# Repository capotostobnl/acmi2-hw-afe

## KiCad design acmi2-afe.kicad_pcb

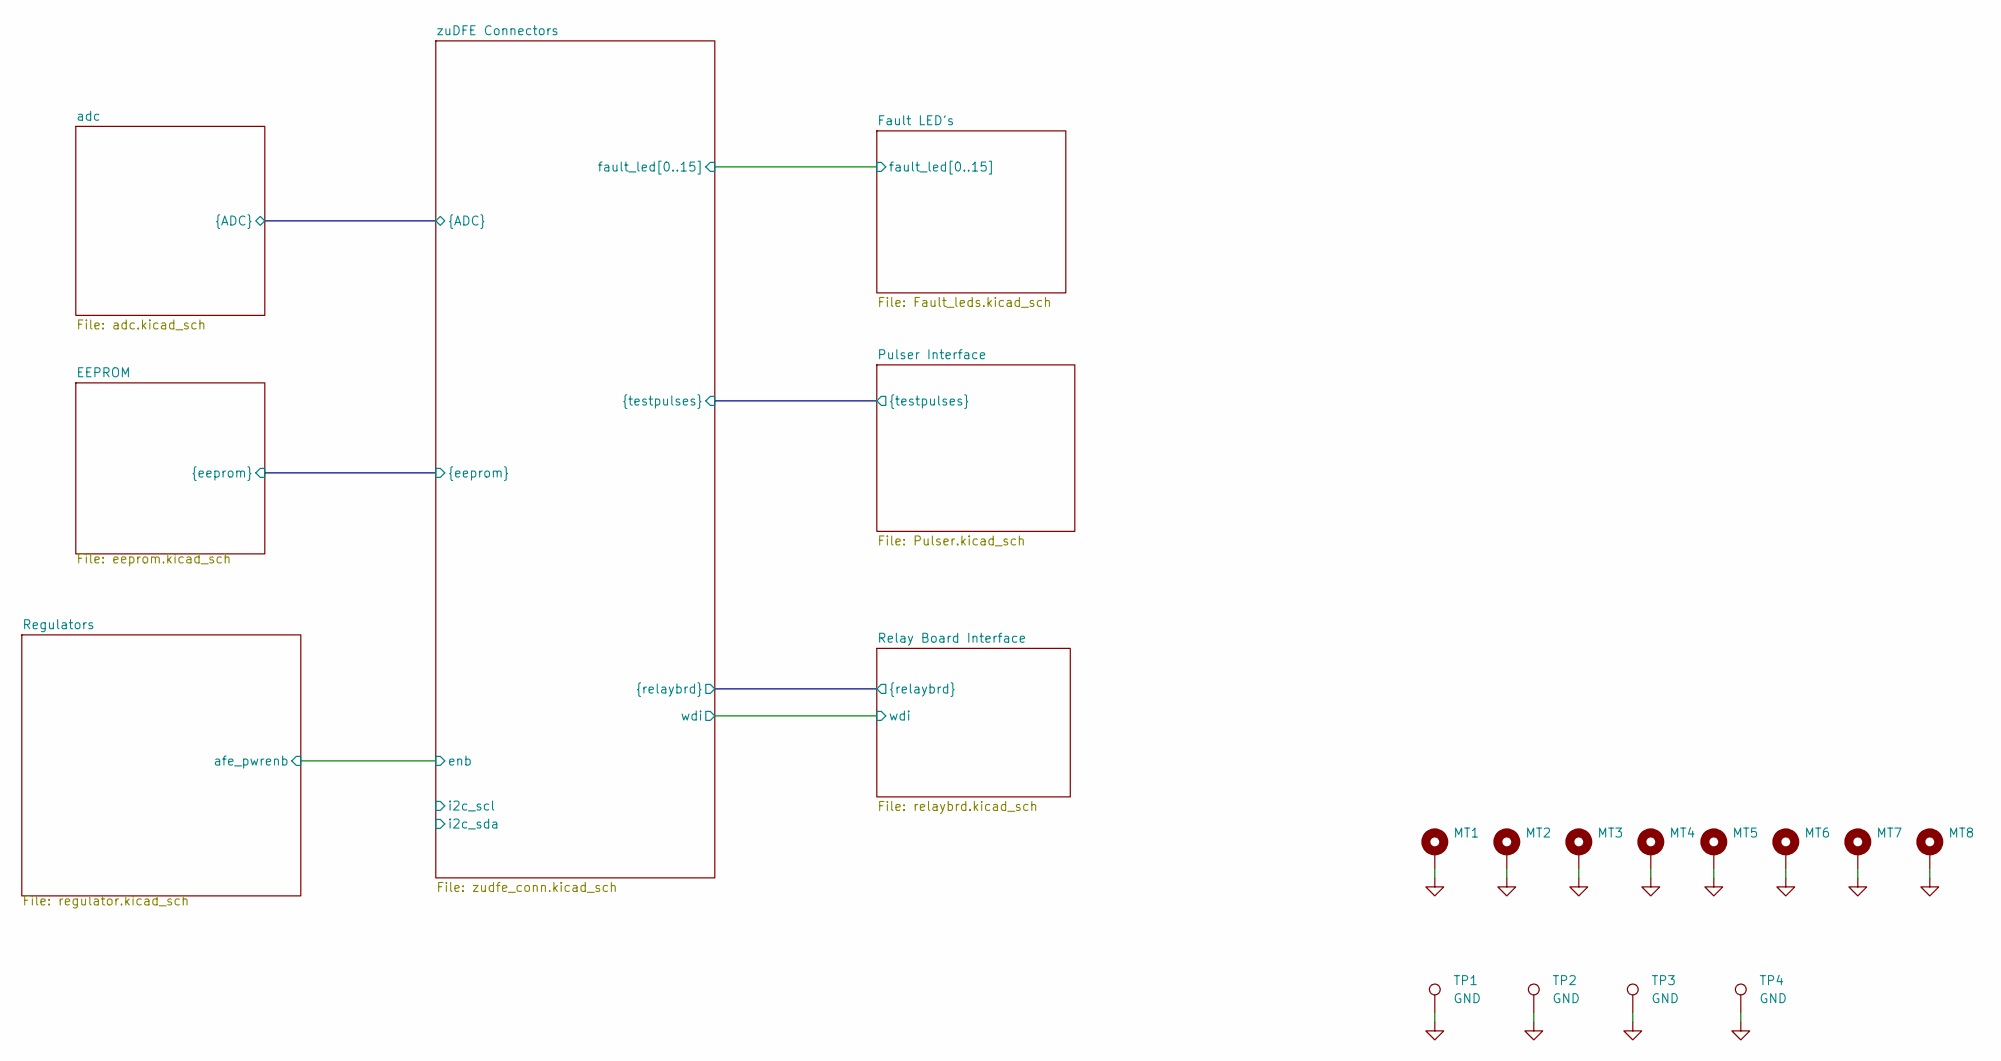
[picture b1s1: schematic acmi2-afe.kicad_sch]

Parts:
MT1, MT2, MT3, MT4, MT5, MT6, MT7, MT8: MountingHole_Pad; MountingHole_4.3mm_M4_DIN965_Pad
TP1, TP2, TP3, TP4: GND; TestPoint_RCS-0C; MFG_PN RCS-0C

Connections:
GND: MT1.1, MT2.1, MT3.1, MT4.1, MT5.1, MT6.1, MT7.1, MT8.1, TP1.1, TP2.1, TP3.1, TP4.1; also elsewhere on the board

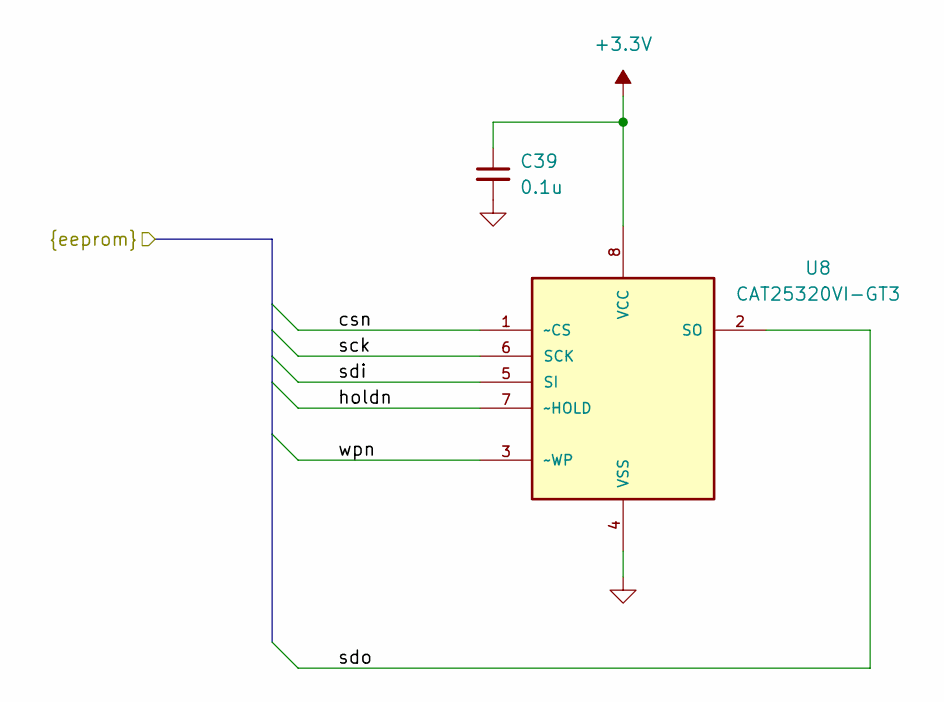
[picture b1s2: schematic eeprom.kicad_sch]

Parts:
C39: 0.1u; C_0805_2012Metric; MFG_PN TMF212B7104KGHT
U8: CAT25320VI-GT3; SOIC127P600X175-8N; MFG_PN CAT25320VI-GT3

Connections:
+3.3V: C39.1, U8.8 (VCC); also elsewhere on the board
/EEPROM/csn: U8.1 (~CS); also elsewhere on the board
/EEPROM/holdn: U8.7 (~HOLD); also elsewhere on the board
/EEPROM/sck: U8.6 (SCK); also elsewhere on the board
/EEPROM/sdi: U8.5 (SI); also elsewhere on the board
/EEPROM/sdo: U8.2 (SO); also elsewhere on the board
/EEPROM/wpn: U8.3 (~WP); also elsewhere on the board
GND: C39.2, U8.4 (VSS); also elsewhere on the board

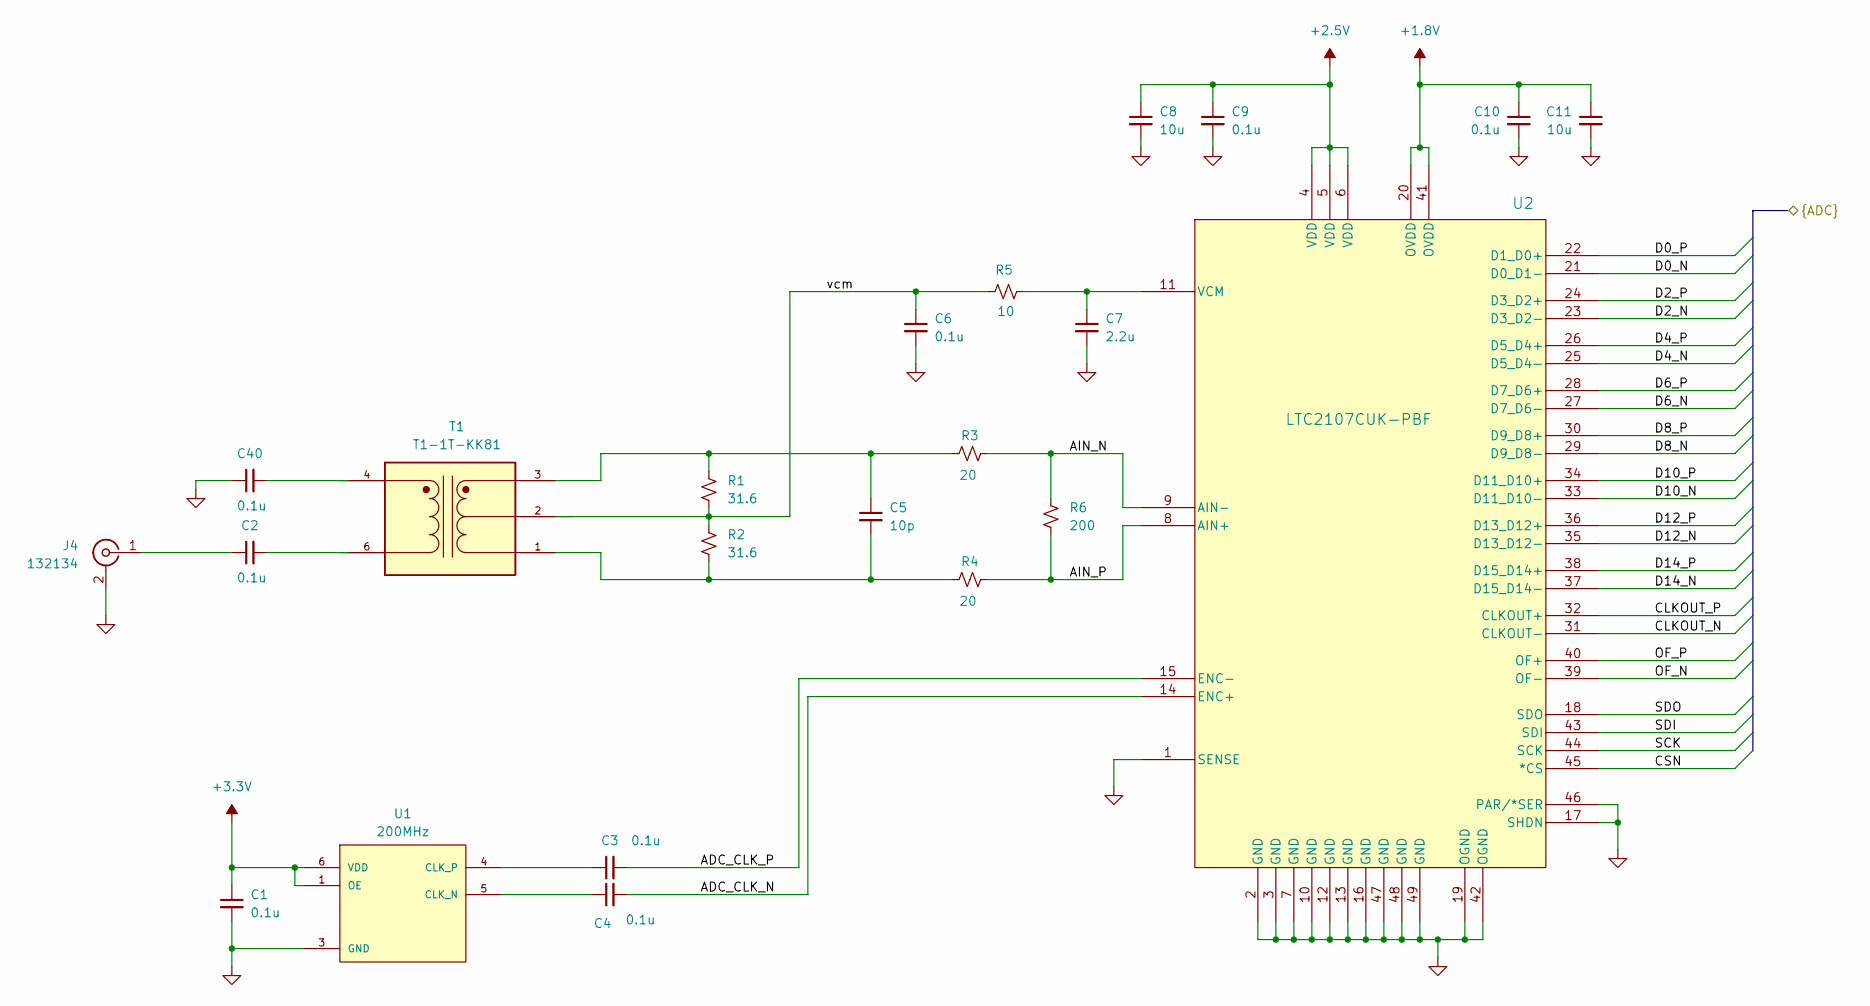
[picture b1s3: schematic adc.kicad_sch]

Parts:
C1, C2, C3, C4, C6, C9, C10, C40: 0.1u; C_0805_2012Metric; MFG_PN TMF212B7104KGHT
C5: 10p; C_0805_2012Metric; MFG_PN QVS212CG100JDHT
C7: 2.2u; C_0805_2012Metric; MFG_PN UMK212BB7225KG-T
C8, C11: 10u; C_0805_2012Metric; MFG_PN GRM21BR61C106KE15K
J4: 132134; SMA_Amphenol_132134_Vertical; MFG_PN 132134
R1, R2: 31.6; R_0805_2012Metric; MFG_PN ERJ-6ENF31R6V
R3, R4: 20; R_0805_2012Metric; MFG_PN ERJ-6ENF20R0V
R5: 10; R_0805_2012Metric; MFG_PN ERJ-6ENF10R0V
R6: 200; R_0805_2012Metric; MFG_PN ERJ-6ENF2000V
T1: T1-1T-KK81; XFMR_T1-1T-KK81_; PARTREV B
U1: 200MHz; OSC_ECS-LVDS33-2000-BN; MFG_PN ECS-LVDS33-2000-BN
U2: LTC2107CUK-PBF; QFN-48_UK_LIT; MFG_PN LTC2107CUK#PBF

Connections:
+1.8V: C10.1, C11.1, U2.20 (OVDD), U2.41 (OVDD); also elsewhere on the board
+2.5V: C8.1, C9.1, U2.4 (VDD), U2.5 (VDD), U2.6 (VDD); also elsewhere on the board
+3.3V: C1.1, U1.1 (OE), U1.6 (VDD); also elsewhere on the board
/adc/ADC_CLK_N: C4.2, U2.14 (ENC+)
/adc/ADC_CLK_P: C3.2, U2.15 (ENC-)
/adc/AIN_N: R3.1, R6.1, U2.9 (AIN-)
/adc/AIN_P: R4.1, R6.2, U2.8 (AIN+)
/adc/CLKOUT_N: U2.31 (CLKOUT-); also elsewhere on the board
/adc/CLKOUT_P: U2.32 (CLKOUT+); also elsewhere on the board
/adc/CSN: U2.45 (*CS); also elsewhere on the board
/adc/D0_N: U2.21 (D0_D1-); also elsewhere on the board
/adc/D0_P: U2.22 (D1_D0+); also elsewhere on the board
/adc/D2_N: U2.23 (D3_D2-); also elsewhere on the board
/adc/D2_P: U2.24 (D3_D2+); also elsewhere on the board
/adc/D4_N: U2.25 (D5_D4-); also elsewhere on the board
/adc/D4_P: U2.26 (D5_D4+); also elsewhere on the board
/adc/D6_N: U2.27 (D7_D6-); also elsewhere on the board
/adc/D6_P: U2.28 (D7_D6+); also elsewhere on the board
/adc/D8_N: U2.29 (D9_D8-); also elsewhere on the board
/adc/D8_P: U2.30 (D9_D8+); also elsewhere on the board
/adc/D10_N: U2.33 (D11_D10-); also elsewhere on the board
/adc/D10_P: U2.34 (D11_D10+); also elsewhere on the board
/adc/D12_N: U2.35 (D13_D12-); also elsewhere on the board
/adc/D12_P: U2.36 (D13_D12+); also elsewhere on the board
/adc/D14_N: U2.37 (D15_D14-); also elsewhere on the board
/adc/D14_P: U2.38 (D15_D14+); also elsewhere on the board
/adc/OF_N: U2.39 (OF-); also elsewhere on the board
/adc/OF_P: U2.40 (OF+); also elsewhere on the board
/adc/SCK: U2.44 (SCK); also elsewhere on the board
/adc/SDI: U2.43 (SDI); also elsewhere on the board
/adc/SDO: U2.18 (SDO); also elsewhere on the board
/adc/vcm: C6.1, R1.2, R2.1, R5.2, T1.2
GND: C1.2, C6.2, C7.2, C8.2, C9.2, C10.2, C11.2, C40.1, J4.2 (Ext), U1.3 (GND), U2.1 (SENSE), U2.2 (GND), U2.3 (GND), U2.7 (GND), U2.10 (GND), U2.12 (GND), U2.13 (GND), U2.16 (GND), U2.17 (SHDN), U2.19 (OGND), U2.42 (OGND), U2.46 (PAR/*SER), U2.47 (GND), U2.48 (GND), U2.49 (GND); also elsewhere on the board
unnamed: C2.2, T1.6
unnamed: C5.1, R1.1, R3.2, T1.3
unnamed: C5.2, R2.2, R4.2, T1.1
unnamed: C40.2, T1.4
unnamed: C2.1, J4.1 (In)
unnamed: C4.1, U1.5 (CLK_N)
unnamed: C3.1, U1.4 (CLK_P)
unnamed: C7.1, R5.1, U2.11 (VCM)

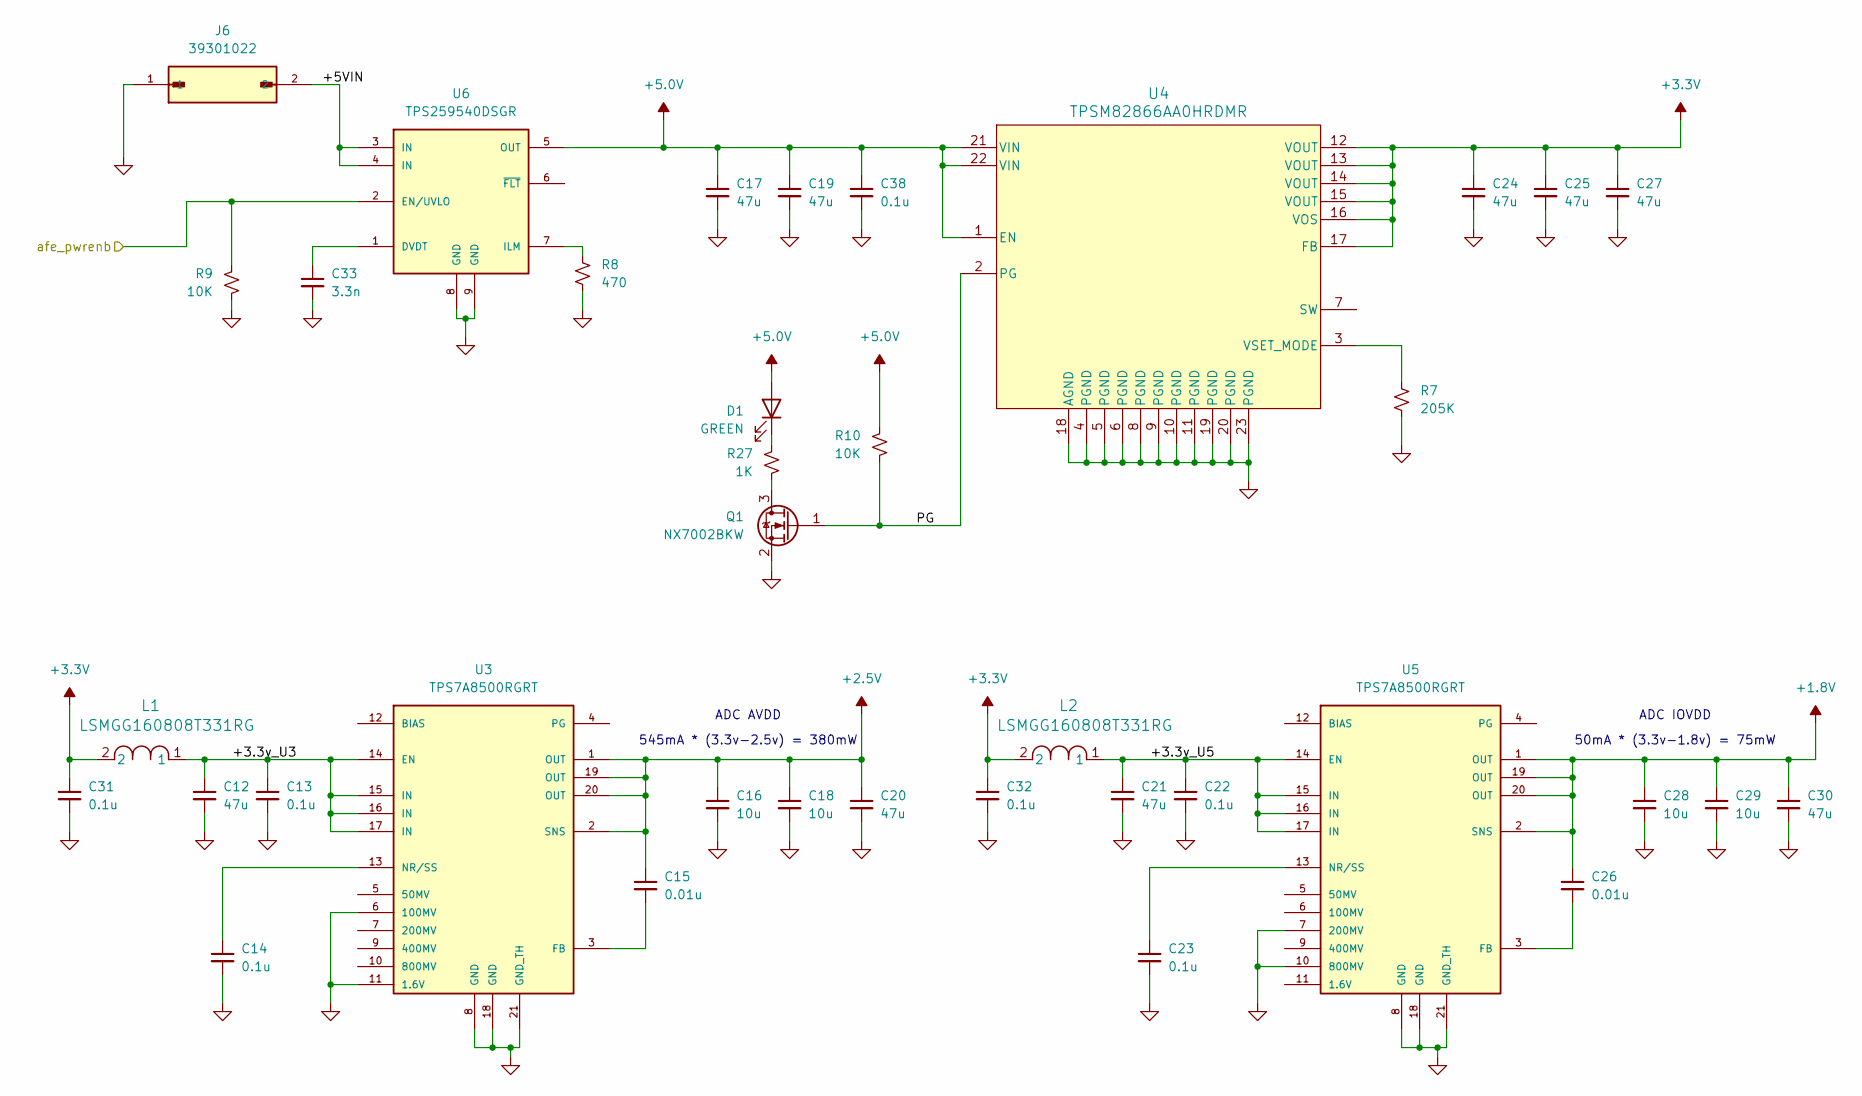
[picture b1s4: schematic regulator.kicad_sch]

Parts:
C12, C17, C19, C20, C21, C24, C25, C27, C30: 47u; C_0805_2012Metric; MFG_PN C2012X5R1A476M125AC
C13, C14, C22, C23, C31, C32, C38: 0.1u; C_0805_2012Metric; MFG_PN TMF212B7104KGHT
C15, C26: 0.01u; C_0805_2012Metric; MFG_PN MAASU21GSL8103MTNA01
C16, C18, C28, C29: 10u; C_0805_2012Metric; MFG_PN GRM21BR61C106KE15K
C33: 3.3n; C_0805_2012Metric; MFG_PN C0805X332K5RECTU
D1: GREEN; LED_0805_2012Metric; MFG_PN LTST-C191KGKT
J6: 39301022; MOLEX_39301022; PARTREV A
L1, L2: LSMGG160808T331RG; IND_LSMG_160808_TAY; MFG_PN LSMGG160808T331RG
Q1: NX7002BKW; SOT-323_SC-70; MFG_PN NX7002BKWX
R7: 205K; R_0805_2012Metric; MFG_PN ERJ-6ENF2053V
R8: 470; R_0805_2012Metric; MFG_PN ERJ-6ENF4700V
R9, R10: 10K; R_0805_2012Metric; MFG_PN ERJ-2RKF1001X
R27: 1K; R_0805_2012Metric; MFG_PN ERJ-P06F1001V
U3, U5: TPS7A8500RGRT; QFN50P350X350X100-21N; MFG_PN TPS7A8500RGRT
U4: TPSM82866AA0HRDMR; RDM0023A-MFG; MFG_PN TPSM82866AA0HRDMR
U6: TPS259540DSGR; SON50P200X200X80-9N; MFG_PN TPS259540DSGR

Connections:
+1.8V: C26.1, C28.1, C29.1, C30.1, U5.1 (OUT), U5.2 (SNS), U5.19 (OUT), U5.20 (OUT); also elsewhere on the board
+2.5V: C15.1, C16.1, C18.1, C20.1, U3.1 (OUT), U3.2 (SNS), U3.19 (OUT), U3.20 (OUT); also elsewhere on the board
+3.3V: C24.1, C25.1, C27.1, C31.1, C32.1, L1.2, L2.2, U4.12 (VOUT), U4.13 (VOUT), U4.14 (VOUT), U4.15 (VOUT), U4.16 (VOS), U4.17 (FB); also elsewhere on the board
+5.0V: C17.1, C19.1, C38.1, D1.2 (A), R10.1, U4.1 (EN), U4.21 (VIN), U4.22 (VIN), U6.5 (OUT); also elsewhere on the board
/Regulators/+3.3v_U3: C12.1, C13.1, L1.1, U3.14 (EN), U3.15 (IN), U3.16 (IN), U3.17 (IN)
/Regulators/+3.3v_U5: C21.1, C22.1, L2.1, U5.14 (EN), U5.15 (IN), U5.16 (IN), U5.17 (IN)
/Regulators/+5VIN: J6.2, U6.3 (IN), U6.4 (IN)
/Regulators/PG: Q1.1 (G), R10.2, U4.2 (PG)
/Regulators/afe_pwrenb: R9.1, U6.2 (EN/UVLO); also elsewhere on the board
GND: C12.2, C13.2, C14.2, C16.2, C17.2, C18.2, C19.2, C20.2, C21.2, C22.2, C23.2, C24.2, C25.2, C27.2, C28.2, C29.2, C30.2, C31.2, C32.2, C33.2, C38.2, J6.1, Q1.2 (S), R7.2, R8.2, R9.2, U3.6 (100MV), U3.8 (GND), U3.11 (1.6V), U3.18 (GND), U3.21 (GND_TH), U4.4 (PGND), U4.5 (PGND), U4.6 (PGND), U4.8 (PGND), U4.9 (PGND), U4.10 (PGND), U4.11 (PGND), U4.18 (AGND), U4.19 (PGND), U4.20 (PGND), U4.23 (PGND), U5.7 (200MV), U5.8 (GND), U5.10 (800MV), U5.18 (GND), U5.21 (GND_TH), U6.8 (GND), U6.9 (GND); also elsewhere on the board
unnamed: D1.1 (K), R27.1
unnamed: Q1.3 (D), R27.2
unnamed: C15.2, U3.3 (FB)
unnamed: C14.1, U3.13 (NR/SS)
unnamed: R7.1, U4.3 (VSET_MODE)
unnamed: C26.2, U5.3 (FB)
unnamed: C23.1, U5.13 (NR/SS)
unnamed: C33.1, U6.1 (DVDT)
unnamed: R8.1, U6.7 (ILM)

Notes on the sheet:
50mA * (3.3v-1.8v) = 75mW
ADC IOVDD
ADC AVDD
545mA * (3.3v-2.5v) = 380mW

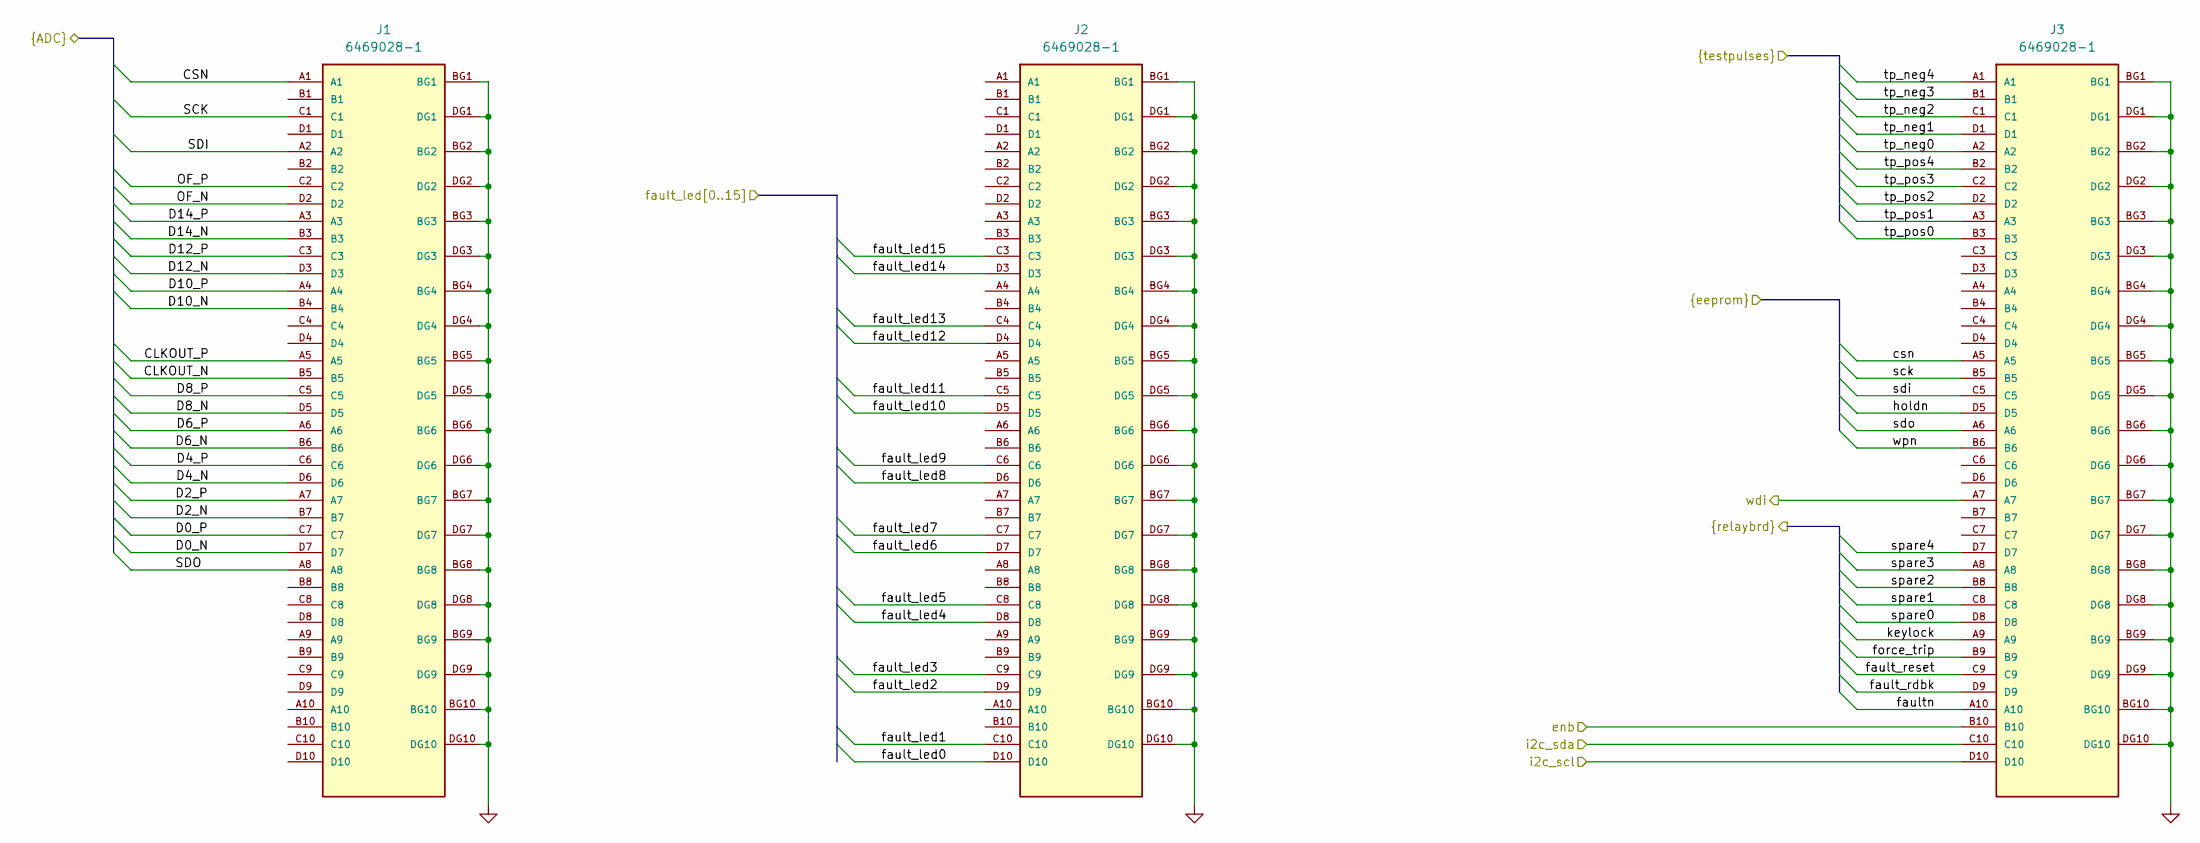
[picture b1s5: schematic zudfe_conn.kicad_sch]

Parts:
J1, J2, J3: 6469028-1; TE_6469028-1; PARTREV E

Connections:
/EEPROM/csn: J3.A5; also elsewhere on the board
/EEPROM/holdn: J3.D5; also elsewhere on the board
/EEPROM/sck: J3.B5; also elsewhere on the board
/EEPROM/sdi: J3.C5; also elsewhere on the board
/EEPROM/sdo: J3.A6; also elsewhere on the board
/EEPROM/wpn: J3.B6; also elsewhere on the board
/Fault LED's/fault_led0: J2.D10; also elsewhere on the board
/Fault LED's/fault_led1: J2.C10; also elsewhere on the board
/Fault LED's/fault_led2: J2.D9; also elsewhere on the board
/Fault LED's/fault_led3: J2.C9; also elsewhere on the board
/Fault LED's/fault_led4: J2.D8; also elsewhere on the board
/Fault LED's/fault_led5: J2.C8; also elsewhere on the board
/Fault LED's/fault_led6: J2.D7; also elsewhere on the board
/Fault LED's/fault_led7: J2.C7; also elsewhere on the board
/Fault LED's/fault_led8: J2.D6; also elsewhere on the board
/Fault LED's/fault_led9: J2.C6; also elsewhere on the board
/Fault LED's/fault_led10: J2.D5; also elsewhere on the board
/Fault LED's/fault_led11: J2.C5; also elsewhere on the board
/Fault LED's/fault_led12: J2.D4; also elsewhere on the board
/Fault LED's/fault_led13: J2.C4; also elsewhere on the board
/Fault LED's/fault_led14: J2.D3; also elsewhere on the board
/Fault LED's/fault_led15: J2.C3; also elsewhere on the board
/Pulser Interface/tp_neg0: J3.A2; also elsewhere on the board
/Pulser Interface/tp_neg1: J3.D1; also elsewhere on the board
/Pulser Interface/tp_neg2: J3.C1; also elsewhere on the board
/Pulser Interface/tp_neg3: J3.B1; also elsewhere on the board
/Pulser Interface/tp_neg4: J3.A1; also elsewhere on the board
/Pulser Interface/tp_pos0: J3.B3; also elsewhere on the board
/Pulser Interface/tp_pos1: J3.A3; also elsewhere on the board
/Pulser Interface/tp_pos2: J3.D2; also elsewhere on the board
/Pulser Interface/tp_pos3: J3.C2; also elsewhere on the board
/Pulser Interface/tp_pos4: J3.B2; also elsewhere on the board
/Regulators/afe_pwrenb: J3.B10; also elsewhere on the board
/Relay Board Interface/fault_rdbk: J3.D9; also elsewhere on the board
/Relay Board Interface/fault_reset: J3.C9; also elsewhere on the board
/Relay Board Interface/faultn: J3.A10; also elsewhere on the board
/Relay Board Interface/force_trip: J3.B9; also elsewhere on the board
/Relay Board Interface/keylock: J3.A9; also elsewhere on the board
/Relay Board Interface/spare0: J3.D8; also elsewhere on the board
/Relay Board Interface/spare1: J3.C8; also elsewhere on the board
/Relay Board Interface/spare2: J3.B8; also elsewhere on the board
/Relay Board Interface/spare3: J3.A8; also elsewhere on the board
/Relay Board Interface/spare4: J3.D7; also elsewhere on the board
/Relay Board Interface/wdi: J3.A7; also elsewhere on the board
/adc/CLKOUT_N: J1.B5; also elsewhere on the board
/adc/CLKOUT_P: J1.A5; also elsewhere on the board
/adc/CSN: J1.A1; also elsewhere on the board
/adc/D0_N: J1.D7; also elsewhere on the board
/adc/D0_P: J1.C7; also elsewhere on the board
/adc/D2_N: J1.B7; also elsewhere on the board
/adc/D2_P: J1.A7; also elsewhere on the board
/adc/D4_N: J1.D6; also elsewhere on the board
/adc/D4_P: J1.C6; also elsewhere on the board
/adc/D6_N: J1.B6; also elsewhere on the board
/adc/D6_P: J1.A6; also elsewhere on the board
/adc/D8_N: J1.D5; also elsewhere on the board
/adc/D8_P: J1.C5; also elsewhere on the board
/adc/D10_N: J1.B4; also elsewhere on the board
/adc/D10_P: J1.A4; also elsewhere on the board
/adc/D12_N: J1.D3; also elsewhere on the board
/adc/D12_P: J1.C3; also elsewhere on the board
/adc/D14_N: J1.B3; also elsewhere on the board
/adc/D14_P: J1.A3; also elsewhere on the board
/adc/OF_N: J1.D2; also elsewhere on the board
/adc/OF_P: J1.C2; also elsewhere on the board
/adc/SCK: J1.C1; also elsewhere on the board
/adc/SDI: J1.A2; also elsewhere on the board
/adc/SDO: J1.A8; also elsewhere on the board
/zuDFE Connectors/i2c_scl: J3.D10
/zuDFE Connectors/i2c_sda: J3.C10
GND: J1.BG1, J1.BG2, J1.BG3, J1.BG4, J1.BG5, J1.BG6, J1.BG7, J1.BG8, J1.BG9, J1.BG10, J1.DG1, J1.DG2, J1.DG3, J1.DG4, J1.DG5, J1.DG6, J1.DG7, J1.DG8, J1.DG9, J1.DG10, J2.BG1, J2.BG2, J2.BG3, J2.BG4, J2.BG5, J2.BG6, J2.BG7, J2.BG8, J2.BG9, J2.BG10, J2.DG1, J2.DG2, J2.DG3, J2.DG4, J2.DG5, J2.DG6, J2.DG7, J2.DG8, J2.DG9, J2.DG10, J3.BG1, J3.BG2, J3.BG3, J3.BG4, J3.BG5, J3.BG6, J3.BG7, J3.BG8, J3.BG9, J3.BG10, J3.DG1, J3.DG2, J3.DG3, J3.DG4, J3.DG5, J3.DG6, J3.DG7, J3.DG8, J3.DG9, J3.DG10; also elsewhere on the board

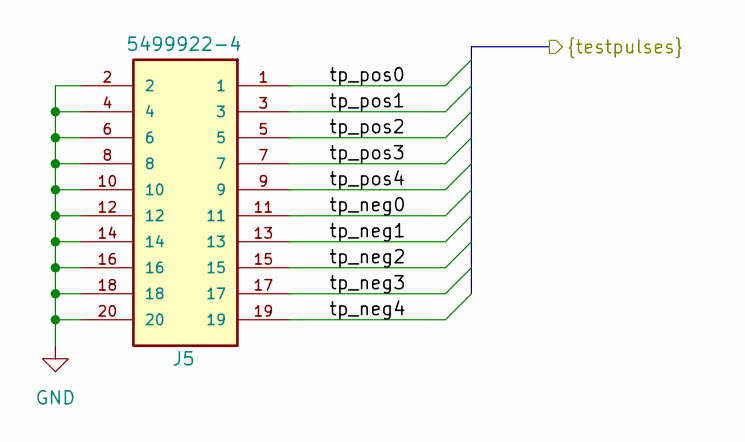
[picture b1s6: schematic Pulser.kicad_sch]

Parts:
J5: 5499922-4; TE_5499922-4; PARTREV R

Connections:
/Pulser Interface/tp_neg0: J5.11; also elsewhere on the board
/Pulser Interface/tp_neg1: J5.13; also elsewhere on the board
/Pulser Interface/tp_neg2: J5.15; also elsewhere on the board
/Pulser Interface/tp_neg3: J5.17; also elsewhere on the board
/Pulser Interface/tp_neg4: J5.19; also elsewhere on the board
/Pulser Interface/tp_pos0: J5.1; also elsewhere on the board
/Pulser Interface/tp_pos1: J5.3; also elsewhere on the board
/Pulser Interface/tp_pos2: J5.5; also elsewhere on the board
/Pulser Interface/tp_pos3: J5.7; also elsewhere on the board
/Pulser Interface/tp_pos4: J5.9; also elsewhere on the board
GND: J5.2, J5.4, J5.6, J5.8, J5.10, J5.12, J5.14, J5.16, J5.18, J5.20; also elsewhere on the board

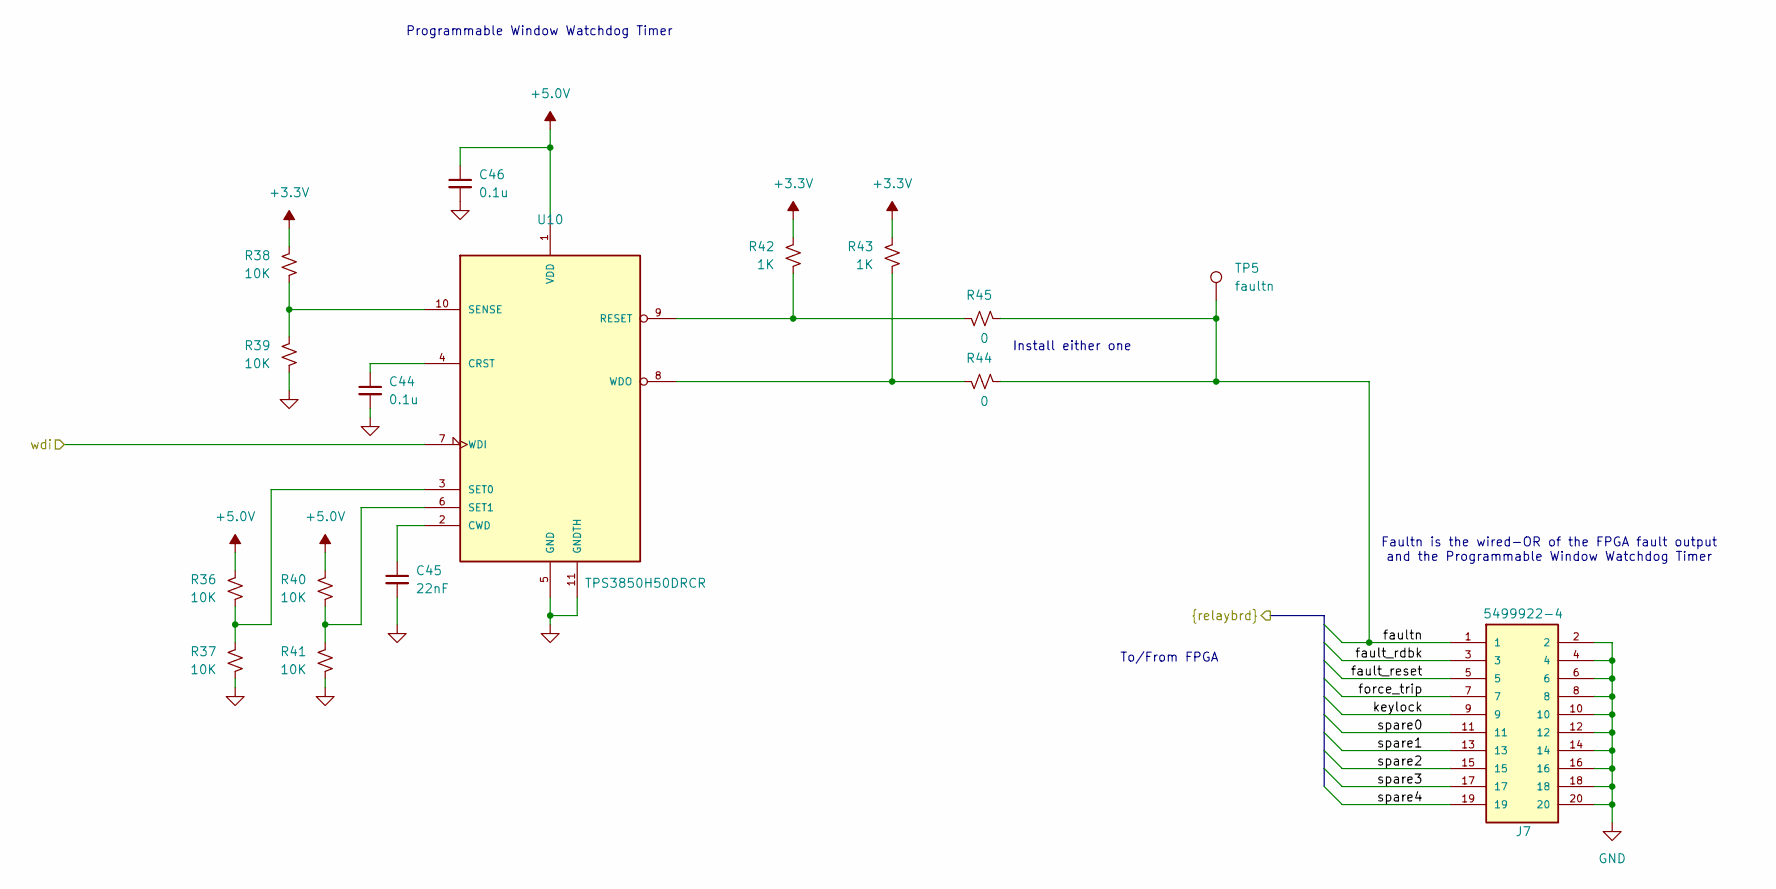
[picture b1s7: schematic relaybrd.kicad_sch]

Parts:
C44, C46: 0.1u; C_0805_2012Metric; MFG_PN TMF212B7104KGHT
C45: 22nF; C_0805_2012Metric; MFG_PN C0805C223J3GEC7210
J7: 5499922-4; TE_5499922-4; PARTREV R
R36, R37, R38, R39, R40, R41: 10K; R_0805_2012Metric; MFG_PN ERJ-2RKF1001X
R42, R43: 1K; R_0805_2012Metric; MFG_PN ERJ-P06F1001V
R44, R45: 0; R_0805_2012Metric; MFG_PN ERJ-2RKF1001X
TP5: faultn; TestPoint_RCS-0C; MFG_PN RCS-0C
U10: TPS3850H50DRCR; TPS3850_DRCR; MFG_PN TPS3850H33DRCR

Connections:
+3.3V: R38.1, R42.1, R43.1; also elsewhere on the board
+5.0V: C46.1, R36.1, R40.1, U10.1 (VDD); also elsewhere on the board
/Relay Board Interface/fault_rdbk: J7.3; also elsewhere on the board
/Relay Board Interface/fault_reset: J7.5; also elsewhere on the board
/Relay Board Interface/faultn: J7.1, R44.2, R45.2, TP5.1; also elsewhere on the board
/Relay Board Interface/force_trip: J7.7; also elsewhere on the board
/Relay Board Interface/keylock: J7.9; also elsewhere on the board
/Relay Board Interface/spare0: J7.11; also elsewhere on the board
/Relay Board Interface/spare1: J7.13; also elsewhere on the board
/Relay Board Interface/spare2: J7.15; also elsewhere on the board
/Relay Board Interface/spare3: J7.17; also elsewhere on the board
/Relay Board Interface/spare4: J7.19; also elsewhere on the board
/Relay Board Interface/wdi: U10.7 (WDI); also elsewhere on the board
GND: C44.2, C45.2, C46.2, J7.2, J7.4, J7.6, J7.8, J7.10, J7.12, J7.14, J7.16, J7.18, J7.20, R37.2, R39.2, R41.2, U10.5 (GND), U10.11 (GNDTH); also elsewhere on the board
unnamed: C44.1, U10.4 (CRST)
unnamed: C45.1, U10.2 (CWD)
unnamed: R42.2, R45.1, U10.9 (RESET)
unnamed: R38.2, R39.1, U10.10 (SENSE)
unnamed: R36.2, R37.1, U10.3 (SET0)
unnamed: R40.2, R41.1, U10.6 (SET1)
unnamed: R43.2, R44.1, U10.8 (WDO)

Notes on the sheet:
To/From FPGA
Faultn is the wired-OR of the FPGA fault output and the Programmable Window Watchdog Timer
Install either one
Programmable Window Watchdog Timer

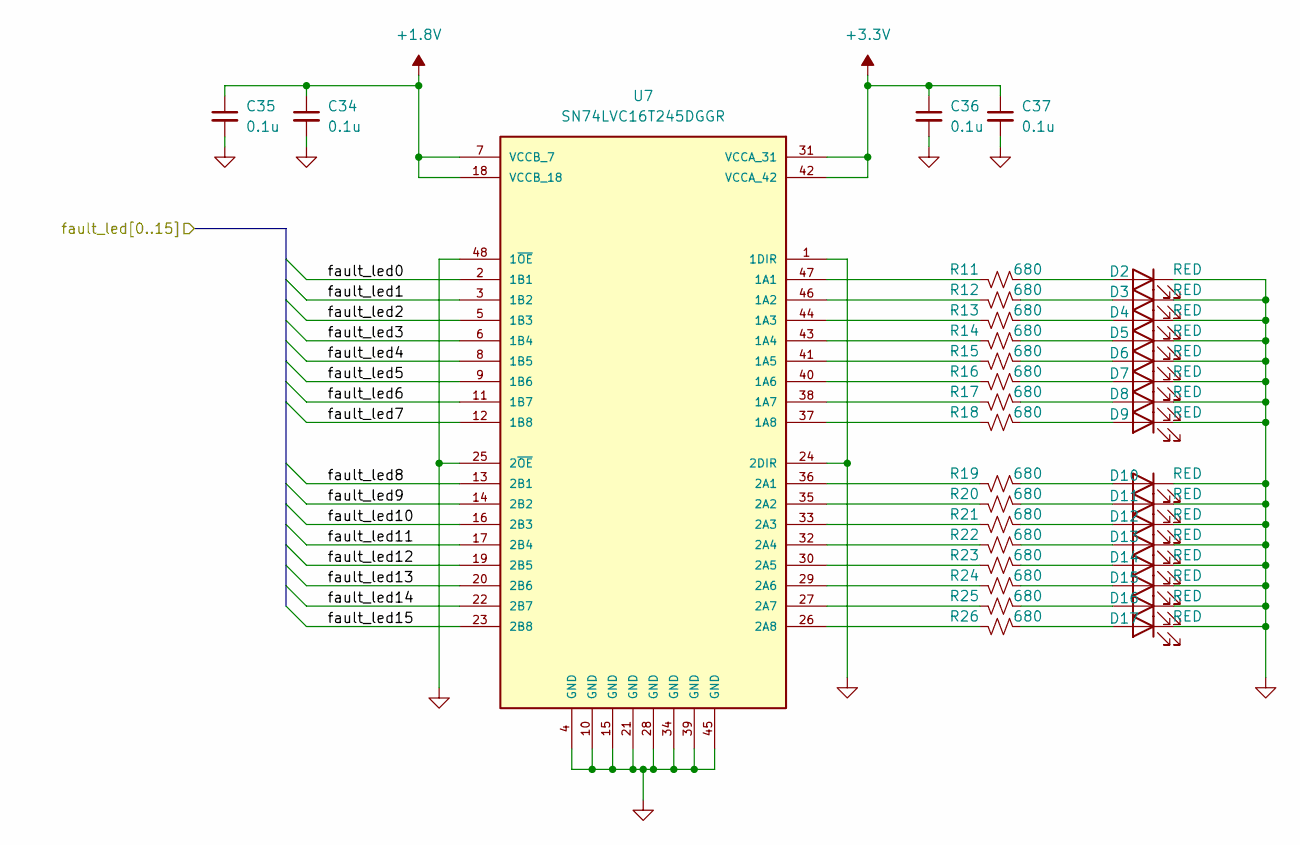
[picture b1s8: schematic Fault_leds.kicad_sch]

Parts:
C34, C35, C36, C37: 0.1u; C_0805_2012Metric; MFG_PN TMF212B7104KGHT
D2, D3, D4, D5, D6, D7, D8, D9, D10, D11, D12, D13, D14, D15, D16, D17: RED; LED_0805_2012Metric; MFG_PN LTST-C191KGKT
R11, R12, R13, R14, R15, R16, R17, R18, R19, R20, R21, R22, R23, R24, R25, R26: 680; R_0805_2012Metric; MFG_PN ERJ-6ENF6800V
U7: SN74LVC16T245DGGR; SOP50P810X120-48N; MFG_PN SN74LVC16T245DGGR

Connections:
+1.8V: C34.1, C35.1, U7.7 (VCCB_7), U7.18 (VCCB_18); also elsewhere on the board
+3.3V: C36.1, C37.1, U7.31 (VCCA_31), U7.42 (VCCA_42); also elsewhere on the board
/Fault LED's/fault_led0: U7.2 (1B1); also elsewhere on the board
/Fault LED's/fault_led1: U7.3 (1B2); also elsewhere on the board
/Fault LED's/fault_led2: U7.5 (1B3); also elsewhere on the board
/Fault LED's/fault_led3: U7.6 (1B4); also elsewhere on the board
/Fault LED's/fault_led4: U7.8 (1B5); also elsewhere on the board
/Fault LED's/fault_led5: U7.9 (1B6); also elsewhere on the board
/Fault LED's/fault_led6: U7.11 (1B7); also elsewhere on the board
/Fault LED's/fault_led7: U7.12 (1B8); also elsewhere on the board
/Fault LED's/fault_led8: U7.13 (2B1); also elsewhere on the board
/Fault LED's/fault_led9: U7.14 (2B2); also elsewhere on the board
/Fault LED's/fault_led10: U7.16 (2B3); also elsewhere on the board
/Fault LED's/fault_led11: U7.17 (2B4); also elsewhere on the board
/Fault LED's/fault_led12: U7.19 (2B5); also elsewhere on the board
/Fault LED's/fault_led13: U7.20 (2B6); also elsewhere on the board
/Fault LED's/fault_led14: U7.22 (2B7); also elsewhere on the board
/Fault LED's/fault_led15: U7.23 (2B8); also elsewhere on the board
GND: C34.2, C35.2, C36.2, C37.2, D2.1 (K), D3.1 (K), D4.1 (K), D5.1 (K), D6.1 (K), D7.1 (K), D8.1 (K), D9.1 (K), D10.1 (K), D11.1 (K), D12.1 (K), D13.1 (K), D14.1 (K), D15.1 (K), D16.1 (K), D17.1 (K), U7.1 (1DIR), U7.4 (GND), U7.10 (GND), U7.15 (GND), U7.21 (GND), U7.24 (2DIR), U7.25 (2~OE), U7.28 (GND), U7.34 (GND), U7.39 (GND), U7.45 (GND), U7.48 (1~OE); also elsewhere on the board
unnamed: D2.2 (A), R11.2
unnamed: D3.2 (A), R12.2
unnamed: D4.2 (A), R13.2
unnamed: D5.2 (A), R14.2
unnamed: D6.2 (A), R15.2
unnamed: D7.2 (A), R16.2
unnamed: D8.2 (A), R17.2
unnamed: D9.2 (A), R18.2
unnamed: D10.2 (A), R19.2
unnamed: D11.2 (A), R20.2
unnamed: D12.2 (A), R21.2
unnamed: D13.2 (A), R22.2
unnamed: D14.2 (A), R23.2
unnamed: D15.2 (A), R24.2
unnamed: D16.2 (A), R25.2
unnamed: D17.2 (A), R26.2
unnamed: R11.1, U7.47 (1A1)
unnamed: R12.1, U7.46 (1A2)
unnamed: R13.1, U7.44 (1A3)
unnamed: R14.1, U7.43 (1A4)
unnamed: R15.1, U7.41 (1A5)
unnamed: R16.1, U7.40 (1A6)
unnamed: R17.1, U7.38 (1A7)
unnamed: R18.1, U7.37 (1A8)
unnamed: R19.1, U7.36 (2A1)
unnamed: R20.1, U7.35 (2A2)
unnamed: R21.1, U7.33 (2A3)
unnamed: R22.1, U7.32 (2A4)
unnamed: R23.1, U7.30 (2A5)
unnamed: R24.1, U7.29 (2A6)
unnamed: R25.1, U7.27 (2A7)
unnamed: R26.1, U7.26 (2A8)

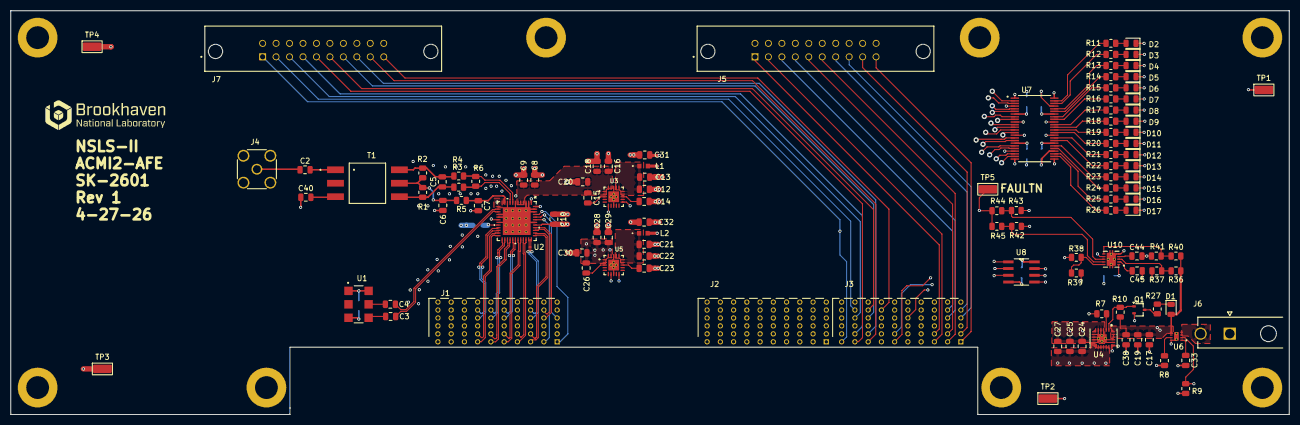
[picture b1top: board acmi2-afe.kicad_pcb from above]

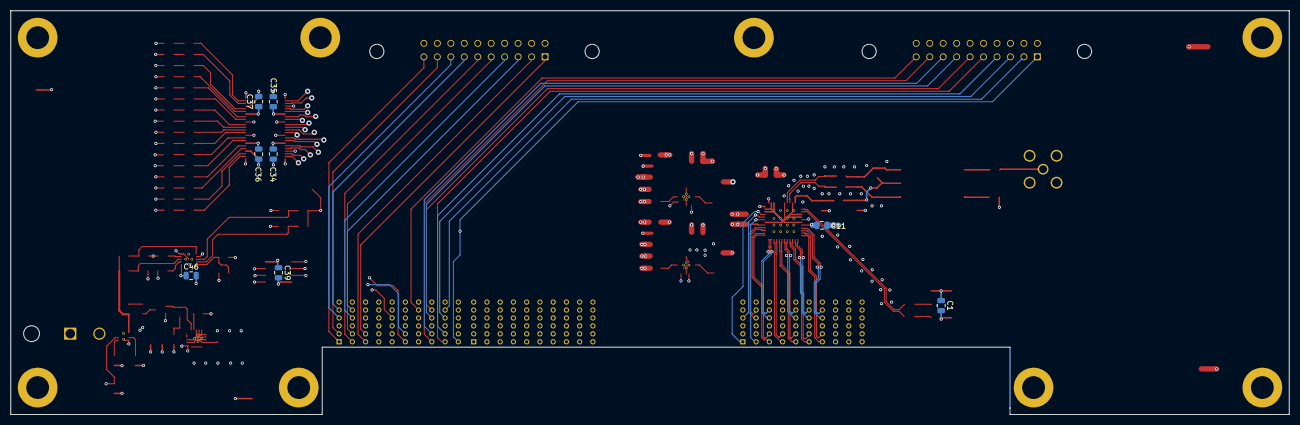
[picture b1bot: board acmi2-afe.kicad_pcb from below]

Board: 6 copper layers, 241.3 x 76.2 mm, 130 parts (8 on the bottom side), 138 nets.
